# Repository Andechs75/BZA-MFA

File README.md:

# BZA-MFA
Vintage 8085 computer for educational purpose

Hi there!
... currently it's just setting up this Git-Hub. A lot of content is under construction.
CMDR Andechs

## Terminal Interface
Arduino Micro VT100 Interface for the MFA and a Terminal program.
- Uses serial pass through between USB at any Serial(TTL-Level) port of the MFA
- Replacement for the Video-Keyboard-Interface
- Supports the original BZA-Editor
- Provides original keyboard-shortcuts
- Modern keyboard use, by macro those keys
- ESC[-sequences (yes, it can colour!)
- Copy-Paste programs between MFA and PC

### Terminal: Preview

### Terminal: Application requirements
- MFA CPU, RAM, ROM, (Serial Card)
- RS232-TTL Level connection (MC1488/89 removed !!) 
- ArduinoMicro
- e.g. PuTTY
- for the BZA-Editor u need to modify the ROM! Nothin hacky! That was original supposed to be a lesson unit ;o) 

### Terminal: Setup hardware
- Remove the Video and Keybord Card.
- Remove the +/-12V driver and receiver. That's the MC1488/89.
- Connect the TTL Rx, Tx, 5V and GND to the Micro D1/Tx, D0/RX, VIN and GND.
  
- modify the ROM: MAT32kT for Serial Card, MAT32kS for Serial on CPU:
  
  The Editor uses a Key-Table. So we only modify this as it was intended to be modified. 
- Burn the Arduino (TTL, if you remember...)

### Terminal: How to use

## Documents
- Collection of BZA-MFA documents
- ROM-Files
- Some Datasheets you always need for reairs

## Attributions
- [www.oldcomputers-ddns.org](https://oldcomputers-ddns.org/public/pub/rechner/mfa_mikrocomputer_fuer_ausbildung/index.html), origin of the documents-folder.

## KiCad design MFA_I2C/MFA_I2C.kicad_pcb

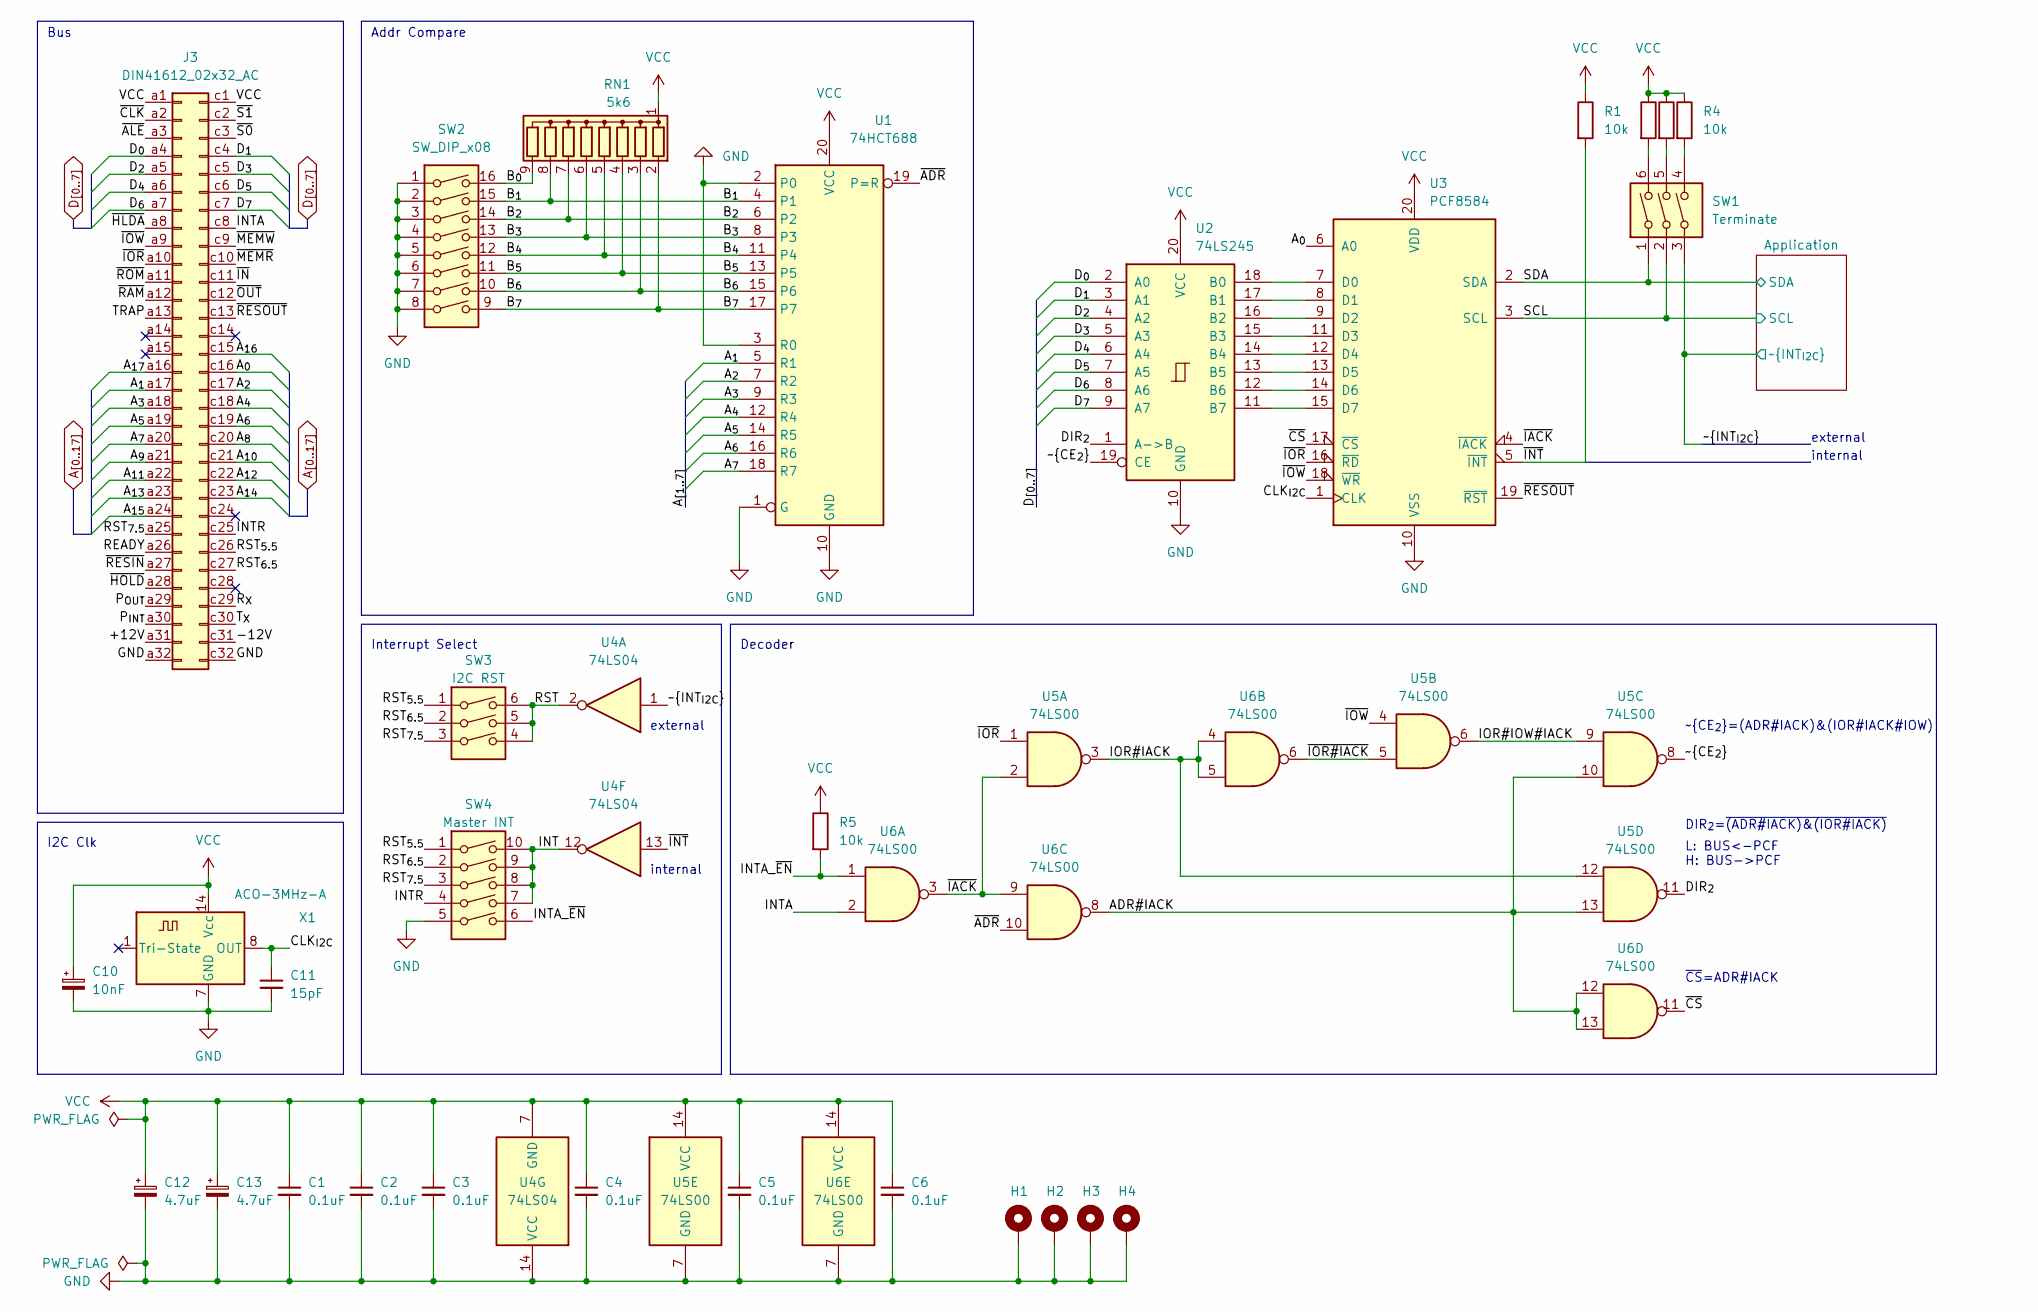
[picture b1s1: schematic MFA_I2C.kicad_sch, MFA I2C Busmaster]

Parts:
C1, C2, C3, C4, C5, C6: 0.1uF; C_Rect_L4.6mm_W2.0mm_P2.50mm_MKS02_FKP02
C10: 10nF; CP_Radial_D4.0mm_P2.00mm
C11: 15pF; C_Rect_L4.6mm_W2.0mm_P2.50mm_MKS02_FKP02
C12, C13: 4.7uF; C_Radial_D4.0mm_H5.0mm_P1.50mm
H1, H2, H3, H4: MountingHole_Pad; MountingHole_3.2mm_M3_ISO14580_Pad
J3: DIN41612_02x32_AC; DIN41612_R_2x32_Male_Horizontal_THT
R1, R2, R3, R4, R5: 10k; R_Axial_DIN0207_L6.3mm_D2.5mm_P7.62mm_Horizontal
RN1: 5k6; R_Array_SIP9
SW1: Terminate; SW_DIP_SPSTx03_Slide_9.78x9.8mm_W7.62mm_P2.54mm
SW2: SW_DIP_x08; SW_DIP_SPSTx08_Slide_9.78x22.5mm_W7.62mm_P2.54mm
SW3: I2C RST; SW_DIP_SPSTx03_Slide_9.78x9.8mm_W7.62mm_P2.54mm
SW4: Master INT; SW_DIP_SPSTx05_Slide_9.78x14.88mm_W7.62mm_P2.54mm
U1: 74HCT688; DIP-20_W7.62mm_Socket
U2: 74LS245; DIP-20_W7.62mm_Socket
U3: PCF8584; DIP-20_W7.62mm_Socket
U4: 74LS04; DIP-14_W7.62mm_Socket
U5, U6: 74LS00; DIP-14_W7.62mm_Socket
X1: ACO-3MHz-A; Oscillator_DIP-14

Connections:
/+12V: J3.a31
/-12V: J3.c31
/ADR#IACK: U5.10, U5.13, U6.8, U6.12, U6.13
/A_{1}: J3.a17, U1.5 (R1)
/A_{2}: J3.c17, U1.7 (R2)
/A_{3}: J3.a18, U1.9 (R3)
/A_{4}: J3.c18, U1.12 (R4)
/A_{5}: J3.a19, U1.14 (R5)
/A_{6}: J3.c19, U1.16 (R6)
/A_{7}: J3.a20, U1.18 (R7)
/B_{0}: RN1.9 (R8), SW2.16
/B_{1}: RN1.8 (R7), SW2.15, U1.4 (P1)
/B_{2}: RN1.7 (R6), SW2.14, U1.6 (P2)
/B_{3}: RN1.6 (R5), SW2.13, U1.8 (P3)
/B_{4}: RN1.5 (R4), SW2.12, U1.11 (P4)
/B_{5}: RN1.4 (R3), SW2.11, U1.13 (P5)
/B_{6}: RN1.3 (R2), SW2.10, U1.15 (P6)
/B_{7}: RN1.2 (R1), SW2.9, U1.17 (P7)
/CLK_{I2C}: C11.1, U3.1 (CLK), X1.8 (OUT)
/DIR_{2}: U2.1 (A->B), U5.11
/INT: SW4.7, SW4.8, SW4.9, SW4.10, U4.12
/INTA: J3.c8, U6.2
/INTA_~EN: R5.2, SW4.6, U6.1
/INTR: J3.c25, SW4.4
/IOR#IACK: U5.3, U5.12, U6.4, U6.5
/IOR#IOW#IACK: U5.6, U5.9
/P_{INT}: J3.a30
/P_{OUT}: J3.a29
/READY: J3.a26
/RST: SW3.4, SW3.5, SW3.6, U4.2
/RST_{5.5}: J3.c26, SW3.1, SW4.1
/RST_{6.5}: J3.c27, SW3.2, SW4.2
/RST_{7.5}: J3.a25, SW3.3, SW4.3
/R_{X}: J3.c29
/SCL: SW1.2, U3.3 (SCL); also elsewhere on the board
/SDA: SW1.1, U3.2 (SDA); also elsewhere on the board
/TRAP: J3.a13
/T_{X}: J3.c30
/~ADR: U1.19 (P=R), U6.10
/~ALE: J3.a3
/~CE_{2}: U2.19 (CE), U5.8
/~CLK: J3.a2
/~CS: U3.17 (~CS), U6.11
/~HLDA: J3.a8
/~HOLD: J3.a28
/~IACK: U3.4 (~IACK), U5.2, U6.3, U6.9
/~INT_{I2C}: SW1.3, U4.1; also elsewhere on the board
/~INT: R1.2, U3.5 (~INT), U4.13
/~IN: J3.c11
/~IOR#IACK: U5.5, U6.6
/~IOR: J3.a10, U3.16 (~RD), U5.1
/~IOW: J3.a9, U3.18 (~WR), U5.4
/~MEMR: J3.c10
/~MEMW: J3.c9
/~OUT: J3.c12
/~RAM: J3.a12
/~RESIN: J3.a27
/~RESOUT: J3.c13, U3.19 (~RST)
/~ROM: J3.a11
/~S0: J3.c3
/~S1: J3.c2
A_{0}: J3.c16, U3.6 (A0)
A_{8}: J3.c20
A_{9}: J3.a21
A_{10}: J3.c21
A_{11}: J3.a22
A_{12}: J3.c22
A_{13}: J3.a23
A_{14}: J3.c23
A_{15}: J3.a24
A_{16}: J3.c15
A_{17}: J3.a16
D_{0}: J3.a4, U2.2 (A0)
D_{1}: J3.c4, U2.3 (A1)
D_{2}: J3.a5, U2.4 (A2)
D_{3}: J3.c5, U2.5 (A3)
D_{4}: J3.a6, U2.6 (A4)
D_{5}: J3.c6, U2.7 (A5)
D_{6}: J3.a7, U2.8 (A6)
D_{7}: J3.c7, U2.9 (A7)
GND: C1.2, C2.2, C3.2, C4.2, C5.2, C6.2, C10.2, C11.2, C12.2, C13.2, H1.1, H2.1, H3.1, H4.1, J3.a32, J3.c32, SW2.1, SW2.2, SW2.3, SW2.4, SW2.5, SW2.6, SW2.7, SW2.8, SW4.5, U1.1 (G), U1.2 (P0), U1.3 (R0), U1.10 (GND), U2.10 (GND), U3.10 (VSS), U4.14 (VCC), U5.7 (GND), U6.7 (GND), X1.7 (GND); also elsewhere on the board
unnamed: R2.2, SW1.6
unnamed: R3.2, SW1.5
unnamed: R4.2, SW1.4
unnamed: U2.11 (B7), U3.15 (D7)
unnamed: U2.12 (B6), U3.14 (D6)
unnamed: U2.13 (B5), U3.13 (D5)
unnamed: U2.14 (B4), U3.12 (D4)
unnamed: U2.15 (B3), U3.11 (D3)
unnamed: U2.16 (B2), U3.9 (D2)
unnamed: U2.17 (B1), U3.8 (D1)
unnamed: U2.18 (B0), U3.7 (D0)
VCC: C1.1, C2.1, C3.1, C4.1, C5.1, C6.1, C10.1, C12.1, C13.1, J3.a1, J3.c1, R1.1, R2.1, R3.1, R4.1, R5.1, RN1.1 (common), U1.20 (VCC), U2.20 (VCC), U3.20 (VDD), U4.7 (GND), U5.14 (VCC), U6.14 (VCC), X1.14 (Vcc); also elsewhere on the board

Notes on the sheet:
Bus
Addr Compare
external
internal
Decoder
I2C Clk
~{CE_{2}}=(ADR#IACK)&(IOR#IACK#IOW)
L: BUS<-PCF H: BUS->PCF
~{CS}=ADR#IACK
DIR_{2}=~{(ADR#IACK)&(IOR#IACK)}
Interrupt Select

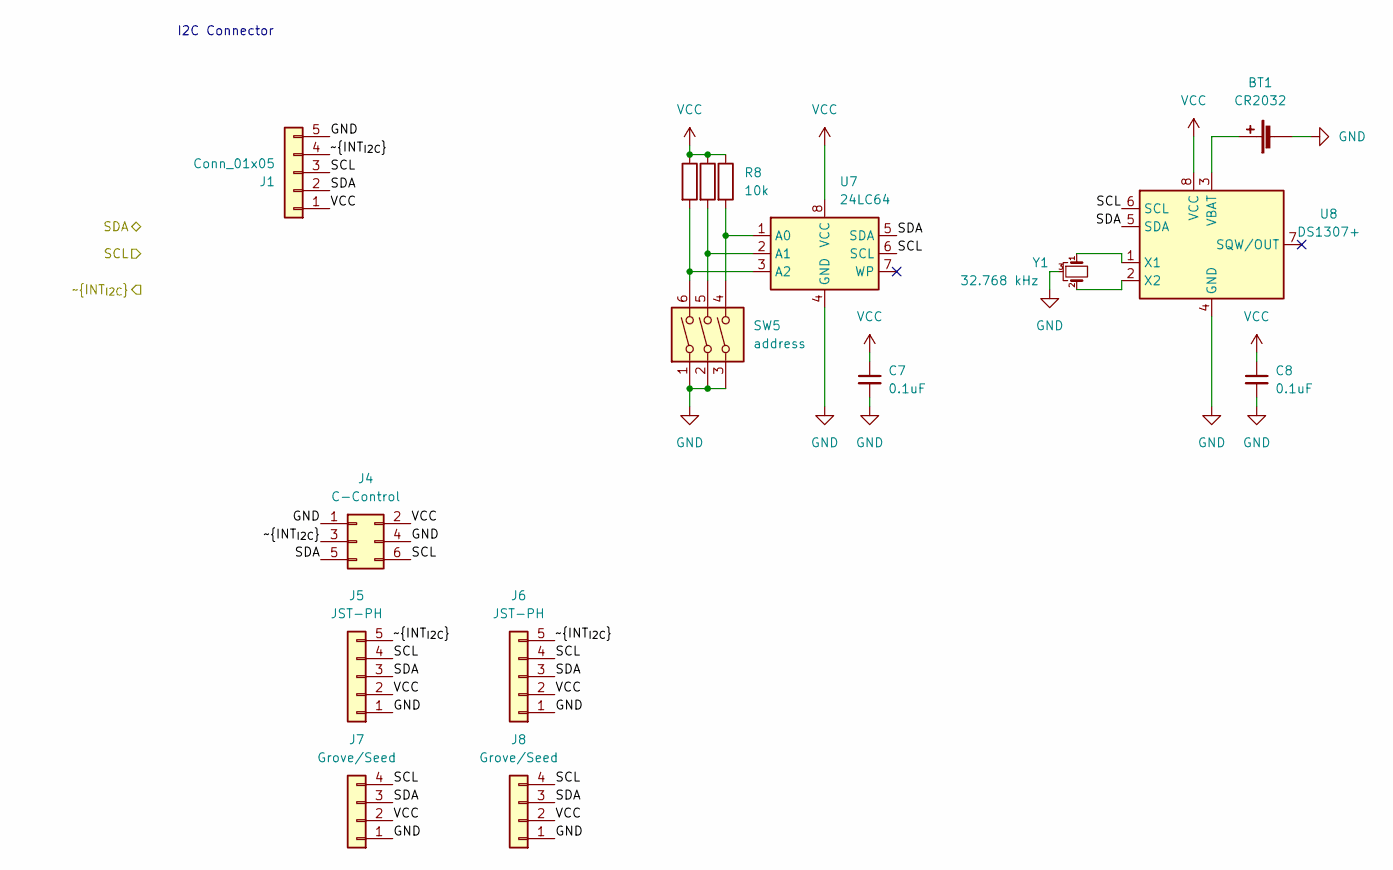
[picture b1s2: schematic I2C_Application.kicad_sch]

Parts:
BT1: CR2032; BatteryHolder_Keystone_103_1x20mm
C7, C8: 0.1uF; C_Rect_L4.6mm_W2.0mm_P2.50mm_MKS02_FKP02
J1: Conn_01x05; PinHeader_1x05_P2.54mm_Vertical
J4: C-Control; IDC-Header_2x03_P2.54mm_Horizontal
J5, J6: JST-PH; JST_PH_S5B-PH-K_1x05_P2.00mm_Horizontal
J7, J8: Grove/Seed; JST_PH_S4B-PH-K_1x04_P2.00mm_Horizontal
R6, R7, R8: 10k; R_Axial_DIN0207_L6.3mm_D2.5mm_P7.62mm_Horizontal
SW5: address; SW_DIP_SPSTx03_Slide_9.78x9.8mm_W7.62mm_P2.54mm
U7: 24LC64; DIP-8_W7.62mm_Socket
U8: DS1307+; DIP-8_W7.62mm_Socket
Y1: 32.768 kHz; Crystal_C38-LF_D3.0mm_L8.0mm_Horizontal_1EP_style2

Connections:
/SCL: J1.3, J4.6, J5.4, J6.4, J7.4, J8.4, U7.6 (SCL), U8.6 (SCL); also elsewhere on the board
/SDA: J1.2, J4.5, J5.3, J6.3, J7.3, J8.3, U7.5 (SDA), U8.5 (SDA); also elsewhere on the board
/~INT_{I2C}: J1.4, J4.3, J5.5, J6.5; also elsewhere on the board
GND: BT1.2 (-), C7.2, C8.2, J1.5, J4.1, J4.4, J5.1, J6.1, J7.1, J8.1, SW5.1, SW5.2, SW5.3, U7.4 (GND), U8.4 (GND), Y1.3; also elsewhere on the board
unnamed: BT1.1 (+), U8.3 (VBAT)
unnamed: R6.2, SW5.6, U7.3 (A2)
unnamed: R7.2, SW5.5, U7.2 (A1)
unnamed: R8.2, SW5.4, U7.1 (A0)
unnamed: U8.1 (X1), Y1.1
unnamed: U8.2 (X2), Y1.2
VCC: C7.1, C8.1, J1.1, J4.2, J5.2, J6.2, J7.2, J8.2, R6.1, R7.1, R8.1, U7.8 (VCC), U8.8 (VCC); also elsewhere on the board

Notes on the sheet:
I2C Connector

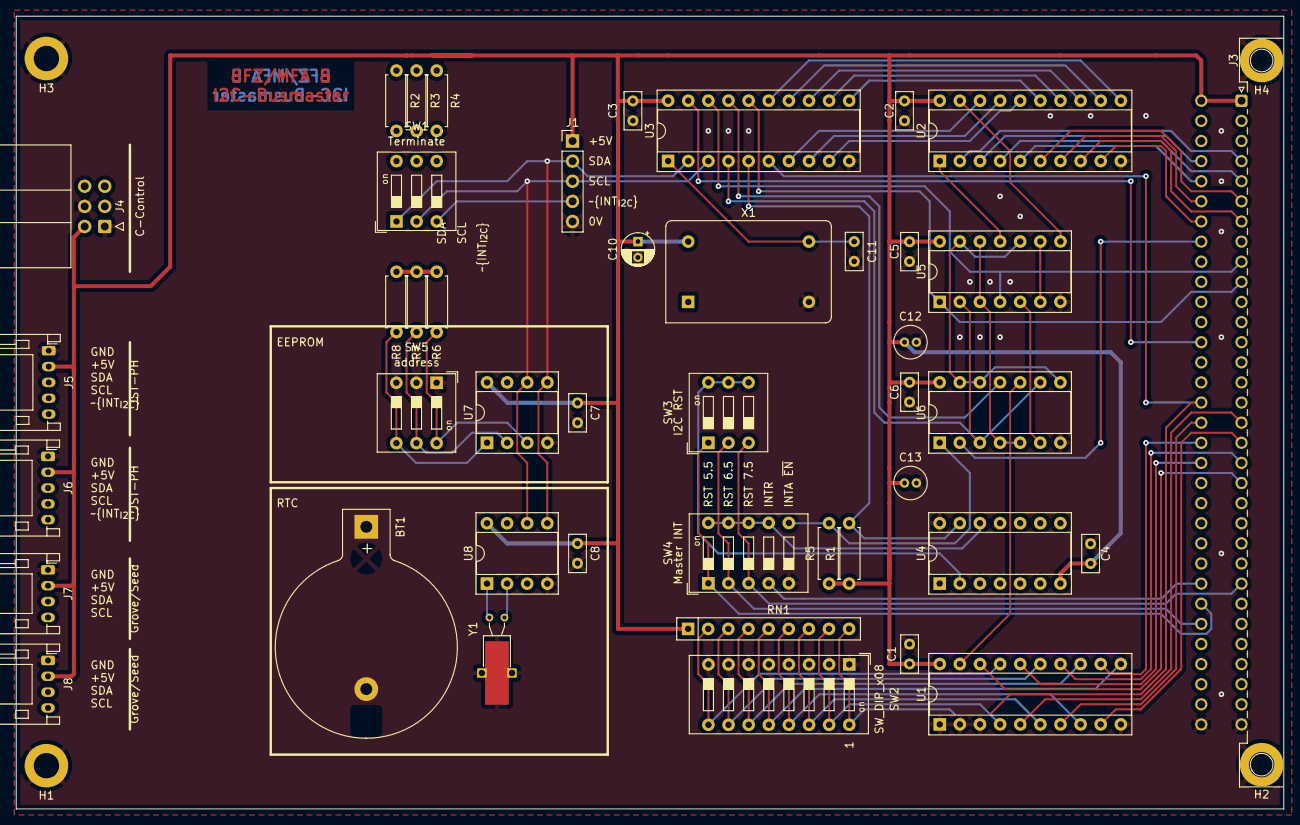
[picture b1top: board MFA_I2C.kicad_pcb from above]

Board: 2 copper layers, 160.0 x 100.1 mm, 48 parts (0 on the bottom side), 68 nets.

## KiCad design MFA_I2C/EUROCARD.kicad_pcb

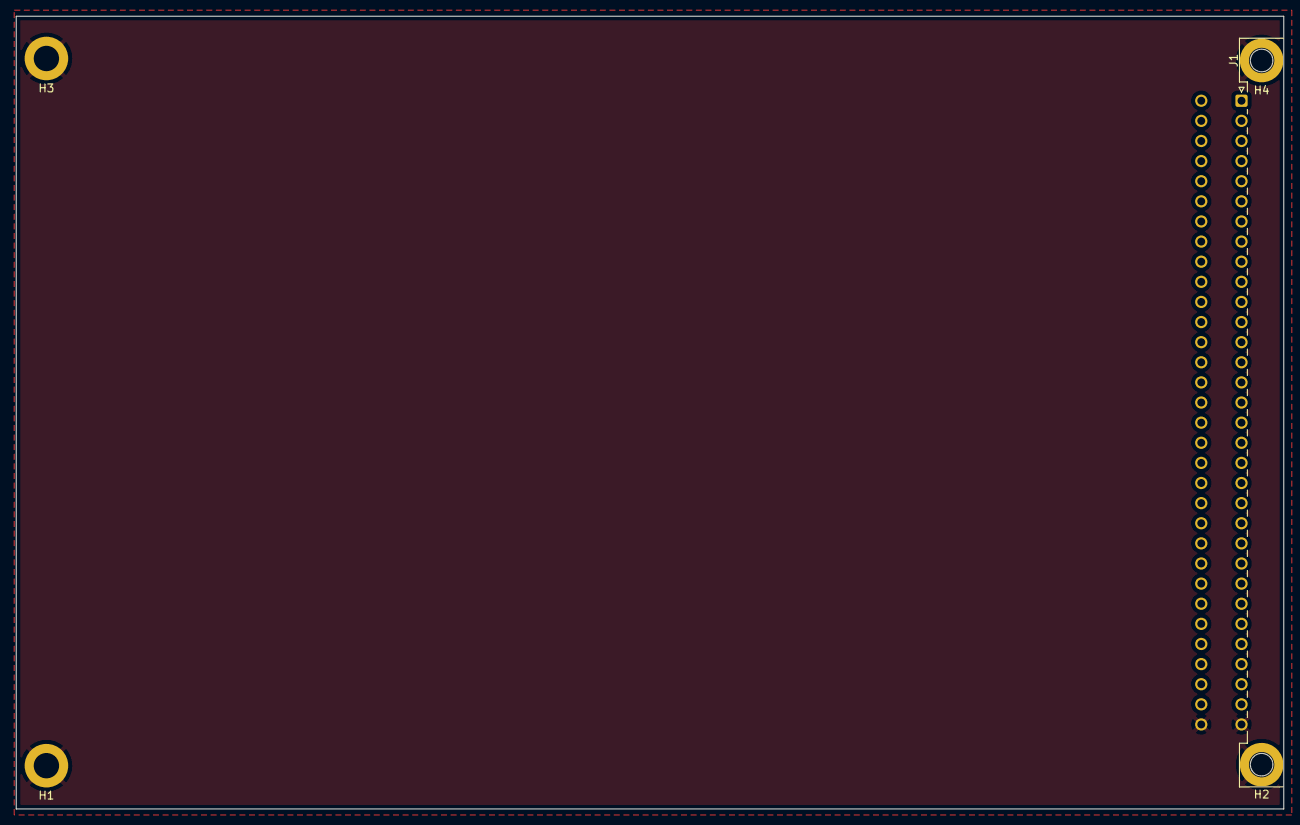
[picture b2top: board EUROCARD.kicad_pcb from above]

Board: 2 copper layers, 160.0 x 100.1 mm, 5 parts (0 on the bottom side), 2 nets, no tracks yet.

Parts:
H1, H2, H3, H4: MountingHole_Pad; MountingHole_3.2mm_M3_ISO14580_Pad
J1: DIN41612_02x32_AC; DIN41612_R_2x32_Male_Horizontal_THT

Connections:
GND: H1.1, H2.1, H3.1, H4.1, J1.a32, J1.c32
VCC: J1.a1, J1.c1

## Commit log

2022-08-03 initial upload
2022-08-03 change folder
2022-08-04 Datasheets
2022-08-04 some more disassembling
2022-08-04 create
2022-08-05 folder sorting
2022-08-18 workspace
2022-08-30 MFA_I2C
2022-09-01 Timing
2022-09-07 changed
2022-09-07 renamed
2022-09-22 next version
